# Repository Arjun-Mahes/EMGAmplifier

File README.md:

made an EMG amplifier PCB from scratch that streams filtered raw and enveloped outputs wirelessly using an ESP32

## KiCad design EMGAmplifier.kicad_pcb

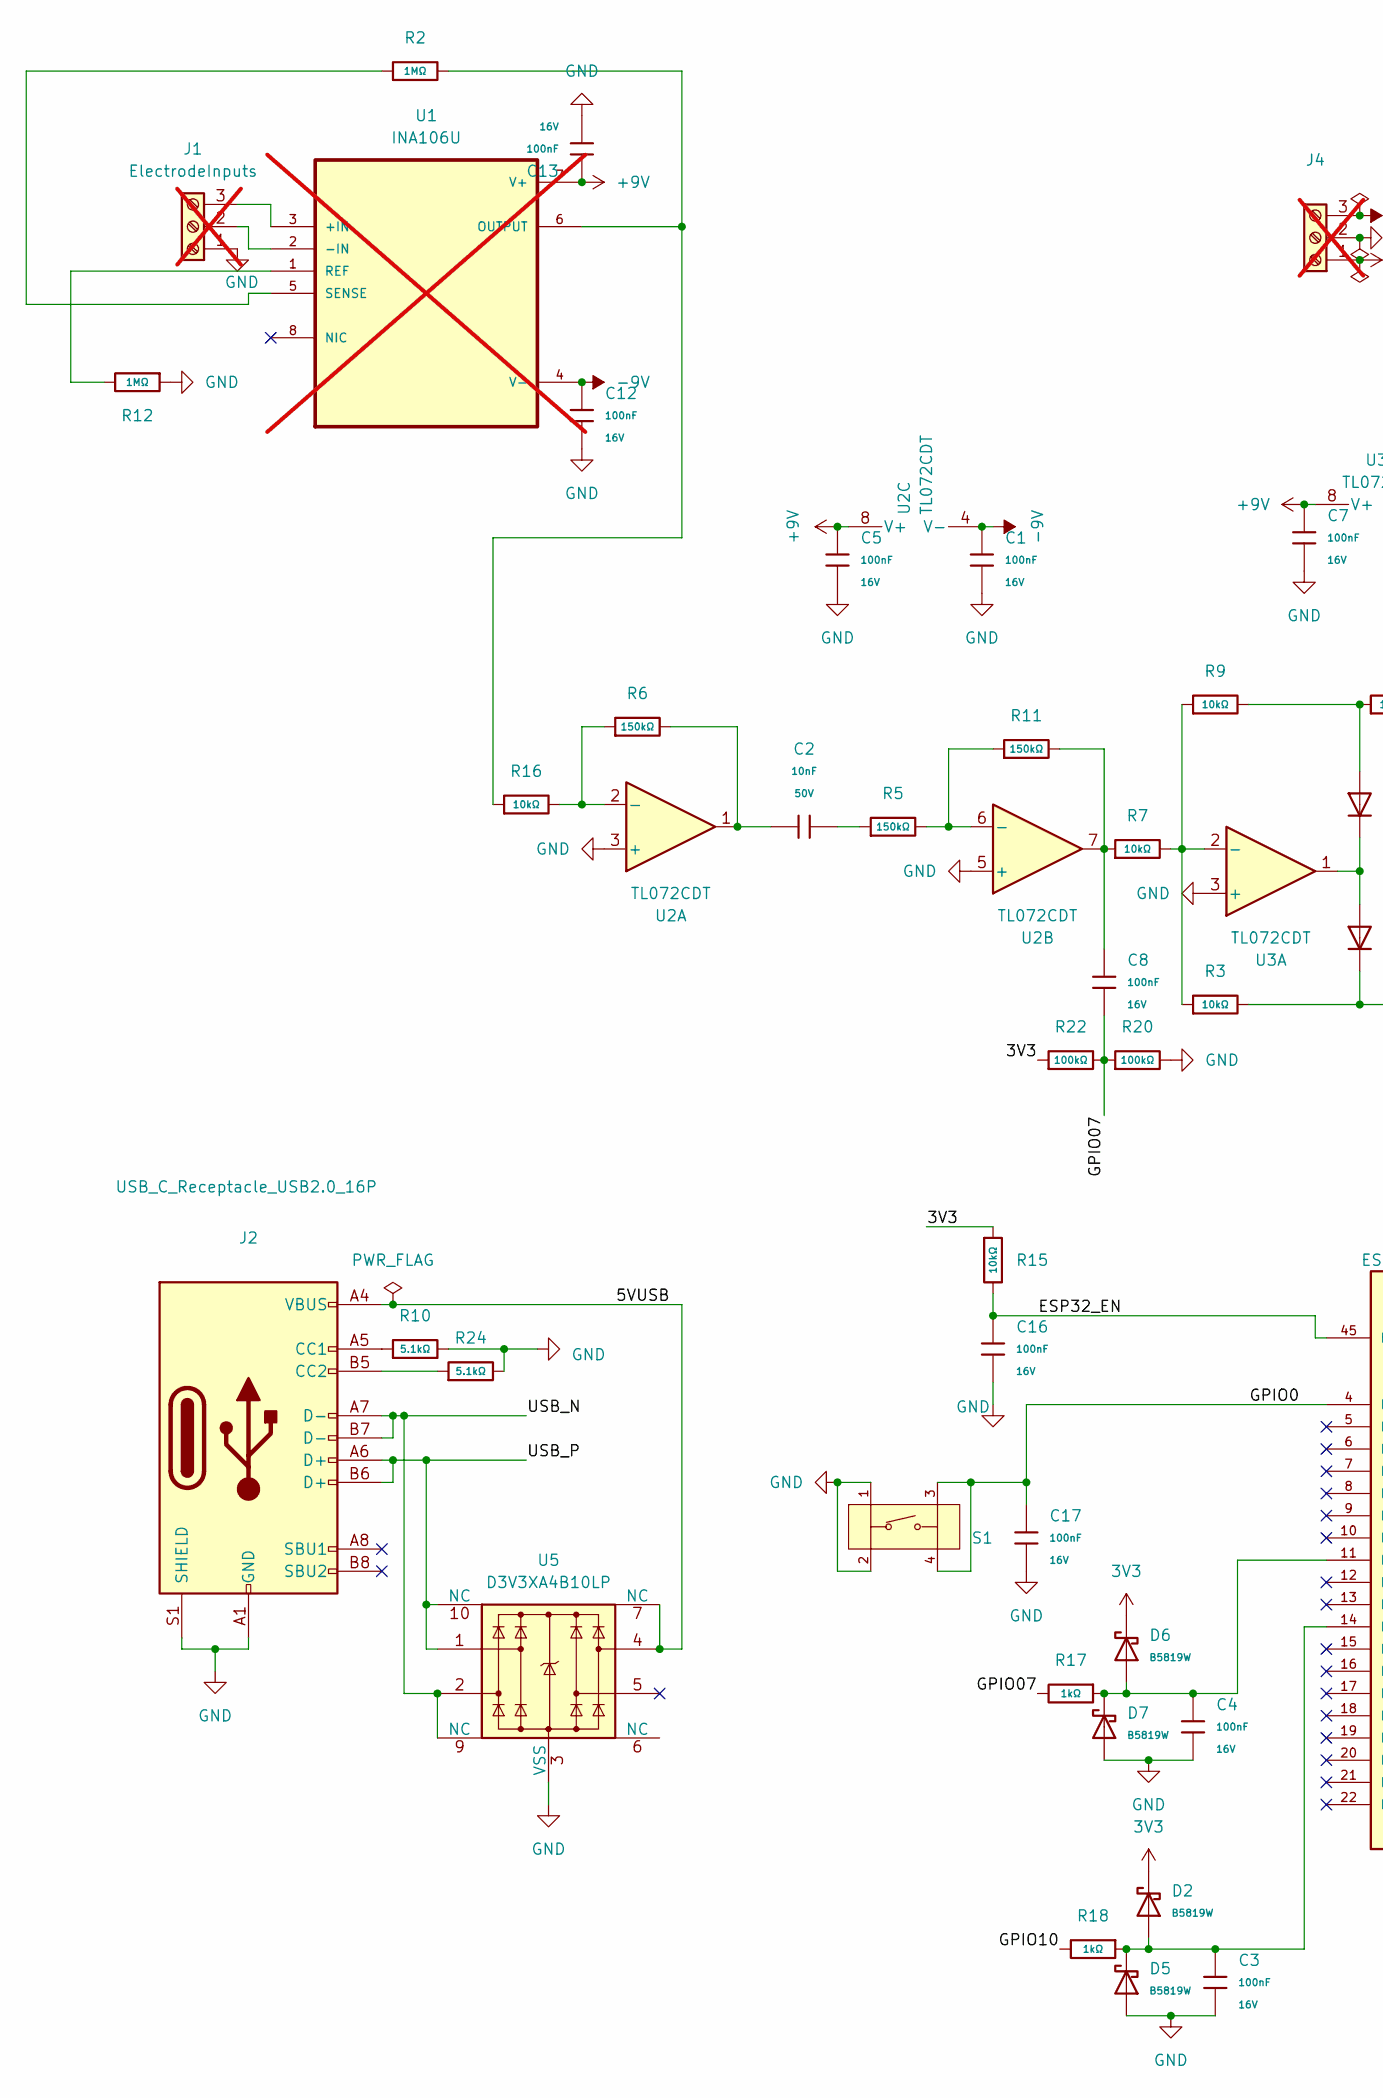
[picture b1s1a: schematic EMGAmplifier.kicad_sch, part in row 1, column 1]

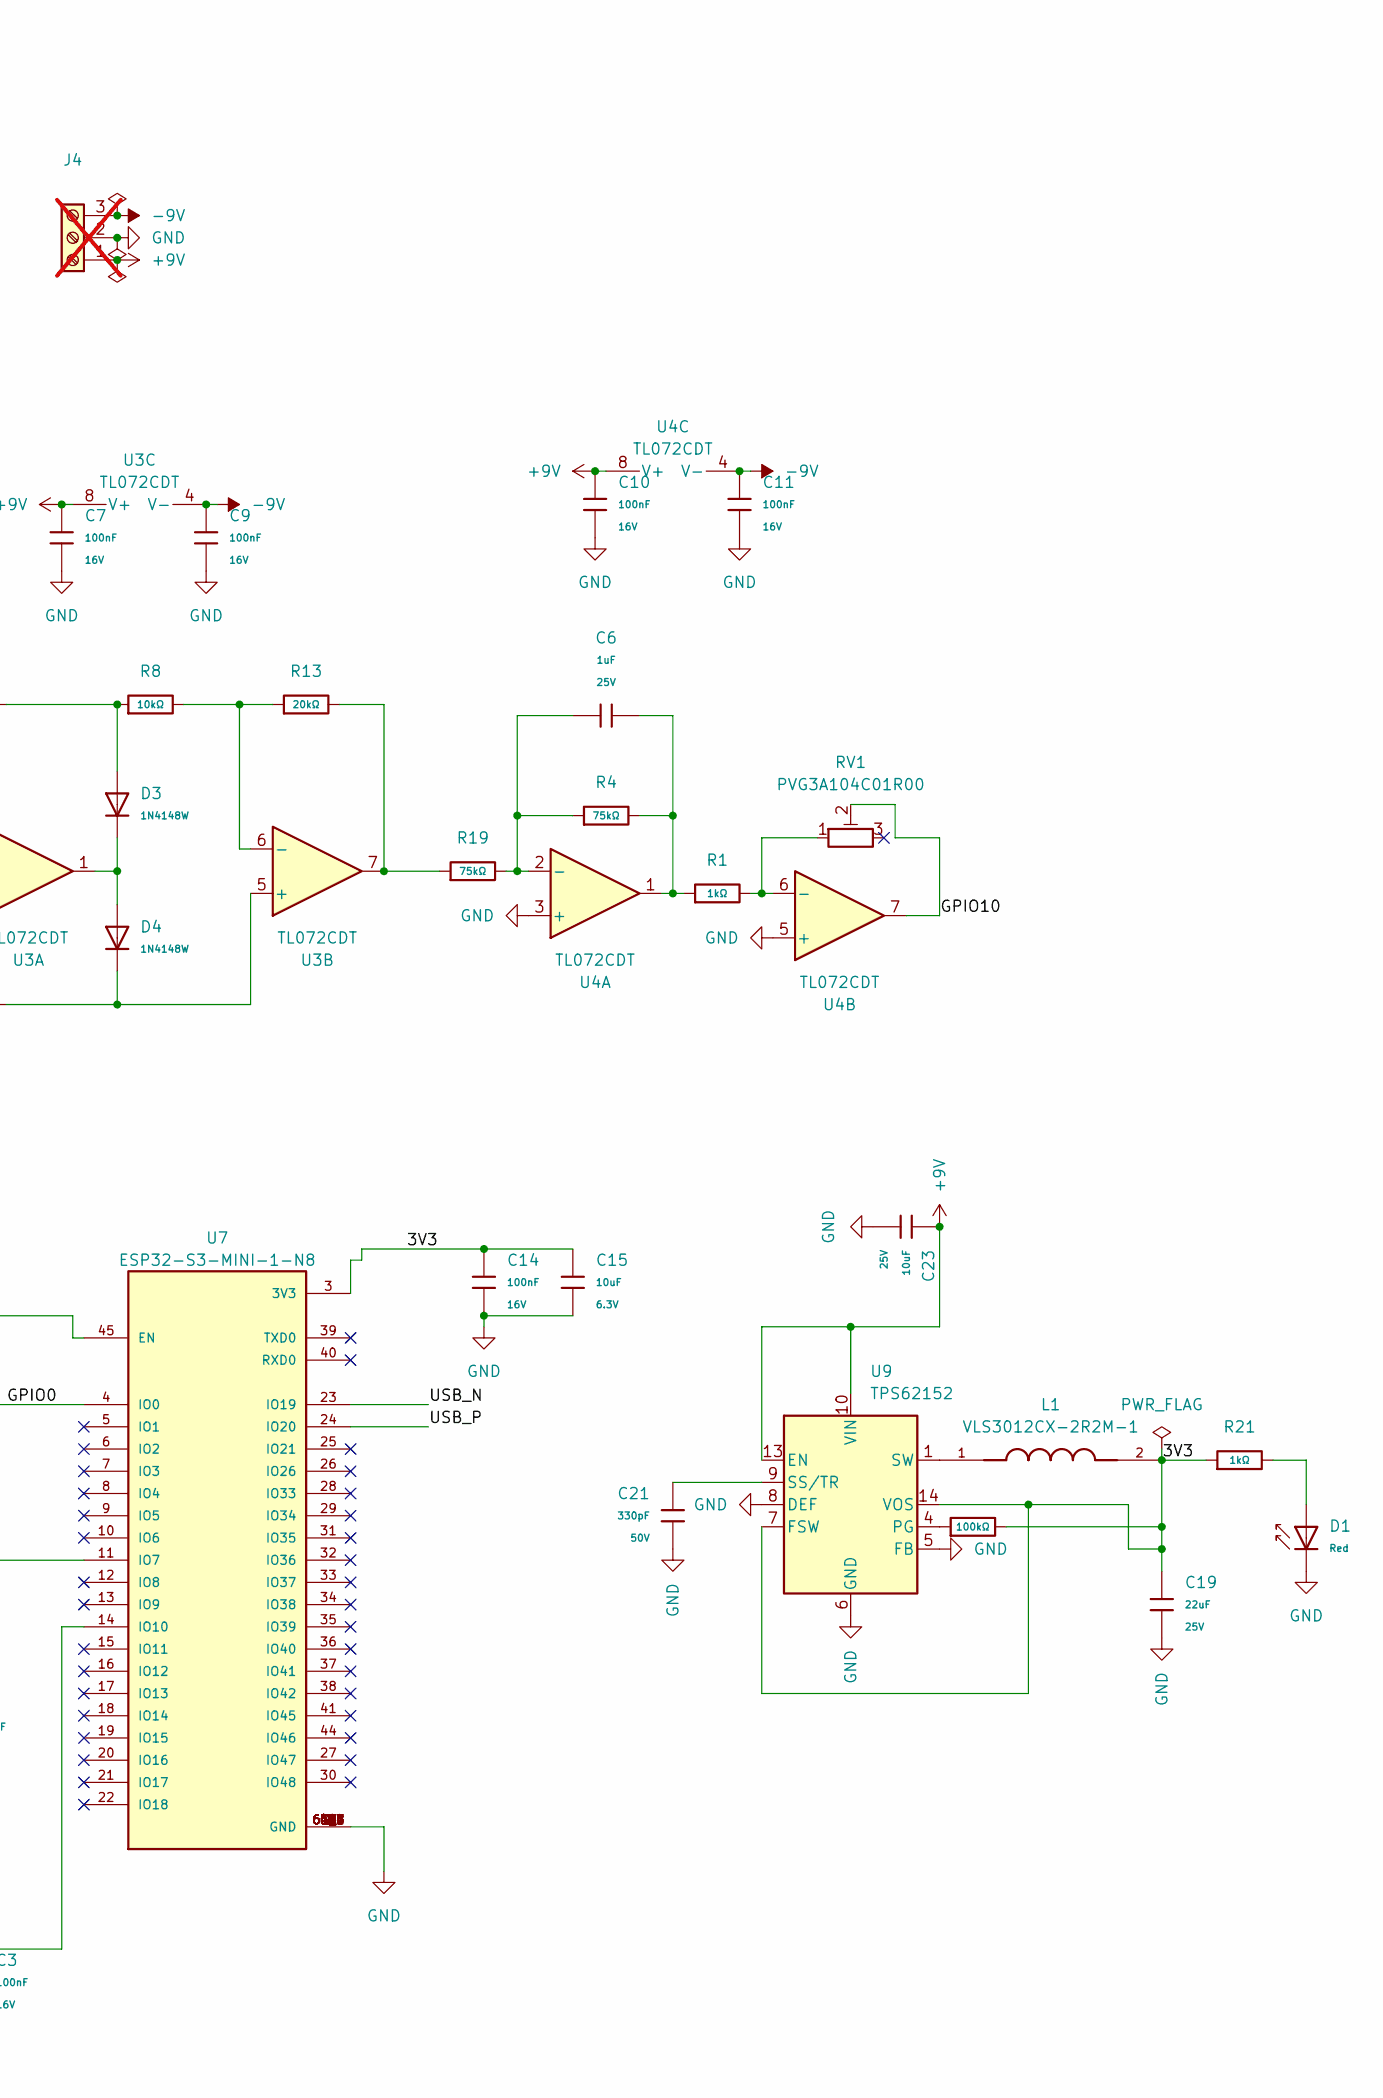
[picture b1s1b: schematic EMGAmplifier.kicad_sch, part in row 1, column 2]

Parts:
C1, C3, C4, C5, C7, C8, C9, C10, C11, C12, C13, C14, C16, C17: 100nF; C_0402; Voltage Rated 16V; Tolerance ±10%; Part CL05B104KO5NNNC; LCSC C1525
C2: 10nF; C_0402; Voltage Rated 50V; Tolerance ±10%; Part CL05B103KB5NNNC; LCSC C15195
C6: 1uF; C_0402; Voltage Rated 25V; Tolerance ±10%; Part CL05A105KA5NQNC; LCSC C52923
C15: 10uF; C_0402; Voltage Rated 6.3V; Tolerance ±20%; Part CL05A106MQ5NUNC; LCSC C15525
C19: 22uF; C_0805; Voltage Rated 25V; Tolerance ±20%; Part CL21A226MAQNNNE; LCSC C45783
C21: 330pF; C_0402; Voltage Rated 50V; Tolerance ±5%; Part CL05C331JB5NNNC; LCSC C13533
C23: 10uF; C_0603; Voltage Rated 25V; Tolerance ±20%; Part CL10A106MA8NRNC; LCSC C96446
D1: Red; D_0603; Part KT-0603R; LCSC C2286
D2, D5, D6, D7: B5819W; D_SOD-123; Forward Voltage (Vf@If) 900mV@3A; Reverse Voltage (Vr) 40V; Part B5819W; LCSC C64885
D3, D4: 1N4148W; D_SOD-123; Forward Voltage (Vf@If) 1V@50mA; Reverse Voltage (Vr) 75V; Part 1N4148W; LCSC C81598
J1: ElectrodeInputs; SAMESKY_TB0011-350-03BE; not fitted
J2: USB_C_Receptacle_USB2.0_16P; USB_C_Receptacle_GCT_USB4105-xx-A_16P_TopMnt_Horizontal; LCSC C3020560
J4: SAMESKY_TB0011-350-03BE; not fitted
L1: VLS3012CX-2R2M-1; IND_VLS3012CX-2R2M-1; PARTREV N/A; LCSC C2683174
R1, R17, R18, R21: 1kΩ; R_0402; Overload Voltage (Max) 50V; Tolerance ±1%; Part 0402WGF1001TCE; LCSC C11702
R2, R12: 1MΩ; R_0402; Overload Voltage (Max) 50V; Tolerance ±1%; Part 0402WGF1004TCE; LCSC C26083
R3, R7, R8, R9, R15, R16: 10kΩ; R_0402; Overload Voltage (Max) 50V; Tolerance ±1%; Part 0402WGF1002TCE; LCSC C25744
R4, R19: 75kΩ; R_0603; Overload Voltage (Max) 75V; Tolerance ±1%; Part 0603WAF7502T5E; LCSC C23242
R5, R6, R11: 150kΩ; R_0603; Overload Voltage (Max) 75V; Tolerance ±1%; Part 0603WAF1503T5E; LCSC C22807
R10, R24: 5.1kΩ; R_0402; Overload Voltage (Max) 50V; Tolerance ±1%; Part 0402WGF5101TCE; LCSC C25905
R13: 20kΩ; R_0402; Overload Voltage (Max) 50V; Tolerance ±1%; Part 0402WGF2002TCE; LCSC C25765
R14, R20, R22: 100kΩ; R_0402; Overload Voltage (Max) 50V; Tolerance ±1%; Part 0402WGF1003TCE; LCSC C25741
RV1: PVG3A104C01R00; RES_C01R00-L; LCSC C5713245
S1: Tactile Button, 160gf; SW-SMD_4P-L5.1-W5.1-P3.70-LS6.5-TL-2; Voltage Rating (Dc) 12V; Part TS-1187A-B-A-B; LCSC C318884
U1: INA106U; SOIC127P599X175-8N; not fitted
U2, U3, U4: TL072CDT; SOIC-8_L5.0-W4.0-P1.27-LS6.0-BL; Voltage - Input Offset(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 3mV; Part TL072CDT; LCSC C6961
U5: D3V3XA4B10LP; Diodes_UDFN-10_1x2.5mm_P0.5mm; LCSC C1980462
U7: ESP32-S3-MINI-1-N8; XCVR_ESP32-S3-MINI-1-N8; PARTREV v0.6; LCSC C2913206
U9: TPS62152; VQFN-16-1EP_3x3mm_P0.5mm_EP1.68x1.68mm_ThermalVias; LCSC C2070611

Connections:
3V3: C14.1, C15.1, C19.1, D2.1, D6.1, L1.2, R14.2, R15.1, R21.1, R22.1, U7.3 (3V3), U9.7 (FSW), U9.14 (VOS)
+9V: C5.1, C7.1, C10.1, C13.1, C23.1, J4.1, U1.7 (V+), U2.8 (V+), U3.8 (V+), U4.8 (V+), U9.10 (VIN), U9.11 (VIN), U9.12 (VIN), U9.13 (EN)
-9V: C1.1, C9.1, C11.1, C12.1, J4.3, U1.4 (V-), U2.4 (V-), U3.4 (V-), U4.4 (V-)
/5VUSB: J2.A4 (VBUS), J2.A9 (VBUS), J2.B4 (VBUS), J2.B9 (VBUS), U5.4, U5.7 (NC)
/ESP32_EN: C16.1, R15.2, U7.45 (EN)
/GPIO0: C17.1, S1.3 (C), S1.4 (D), U7.4 (IO0)
/GPIO07: C8.2, R17.2, R20.1, R22.2
/GPIO10: R18.2, RV1.2, U4.7
/USB_N: J2.A7 (D-), J2.B7 (D-), U5.2, U5.9 (NC), U7.23 (IO19)
/USB_P: J2.A6 (D+), J2.B6 (D+), U5.1, U5.10 (NC), U7.24 (IO20)
GND: C1.2, C3.2, C4.2, C5.2, C7.2, C9.2, C10.2, C11.2, C12.2, C13.2, C14.2, C15.2, C16.2, C17.2, C19.2, C21.2, C23.2, D1.1, D5.2, D7.2, J1.1, J2.A1 (GND), J2.A12 (GND), J2.B1 (GND), J2.B12 (GND), J2.S1 (SHIELD), J4.2, R10.2, R12.1, R20.2, R24.2, S1.1 (A), S1.2 (B), U2.3 (+), U2.5 (+), U3.3 (+), U4.3 (+), U4.5 (+), U5.3 (VSS), U5.8 (VSS), U7.1 (GND), U7.2 (GND), U7.42 (GND), U7.43 (GND), U7.46 (GND), U7.47 (GND), U7.48 (GND), U7.49 (GND), U7.50 (GND), U7.51 (GND), U7.52 (GND), U7.53 (GND), U7.54 (GND), U7.55 (GND), U7.56 (GND), U7.57 (GND), U7.58 (GND), U7.59 (GND), U7.60 (GND), U7.61 (GND), U7.61_1 (GND), U7.61_2 (GND), U7.61_3 (GND), U7.61_4 (GND), U7.61_5 (GND), U7.61_6 (GND), U7.61_7 (GND), U7.61_8 (GND), U7.62 (GND), U7.63 (GND), U7.64 (GND), U7.65 (GND), U9.5 (FB), U9.6 (GND), U9.8 (DEF), U9.15 (GND), U9.16 (GND), U9.17 (GND)
unnamed: C2.1, R6.2, U2.1
unnamed: C2.2, R5.1
unnamed: C6.2, R1.1, R4.2, U4.1
unnamed: C8.1, R7.1, R11.2, U2.7
unnamed: D1.2, R21.2
unnamed: D3.1, D4.2, U3.1
unnamed: D3.2, R8.1, R9.2
unnamed: J1.2, U1.2 (-IN)
unnamed: J1.3, U1.3 (+IN)
unnamed: J2.A5 (CC1), R10.1
unnamed: J2.B5 (CC2), R24.1
unnamed: L1.1, U9.1 (SW), U9.2 (SW), U9.3 (SW)
unnamed: R13.2, R19.1, U3.7
unnamed: R2.2, R16.1, U1.6 (OUTPUT)
unnamed: R12.2, U1.1 (REF)
unnamed: R2.1, U1.5 (SENSE)
unnamed: R6.1, R16.2, U2.2 (-)
unnamed: R5.2, R11.1, U2.6 (-)
unnamed: R3.1, R7.2, R9.1, U3.2 (-)
unnamed: D4.1, R3.2, U3.5 (+)
unnamed: R8.2, R13.1, U3.6 (-)
unnamed: C6.1, R4.1, R19.2, U4.2 (-)
unnamed: R1.2, RV1.1, U4.6 (-)
unnamed: C4.1, D6.2, D7.1, R17.1, U7.11 (IO7)
unnamed: C3.1, D2.2, D5.1, R18.1, U7.14 (IO10)
unnamed: R14.1, U9.4 (PG)
unnamed: C21.1, U9.9 (SS/TR)

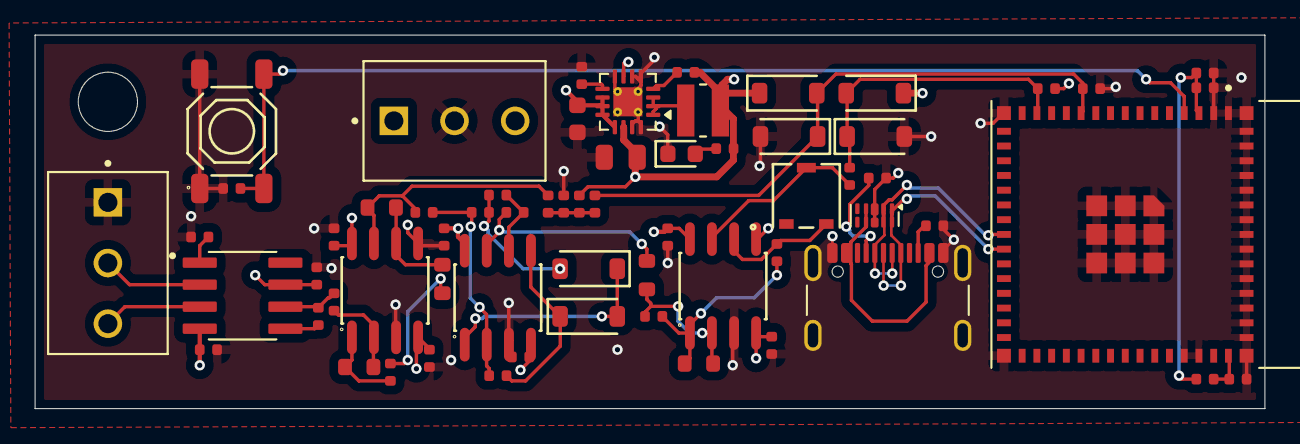
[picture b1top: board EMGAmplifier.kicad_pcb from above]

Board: 4 copper layers, 71.0 x 21.6 mm, 63 parts (0 on the bottom side), 38 nets.

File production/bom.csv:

Designator,Footprint,Quantity,Value,LCSC Part #
"C1, C10, C11, C12, C13, C14, C16, C17, C3, C5, C7, C9",C_0402,12,100nF,C1525
C15,C_0402,1,10uF,C15525
C19,C_0805,1,22uF,C45783
C2,C_0402,1,10nF,C15195
C21,C_0402,1,330pF,C13533
C23,C_0603,1,10uF,C96446
C6,C_0402,1,1uF,C52923
D1,D_0603,1,Red,C2286
"D2, D5",D_SOD-123,2,B5819W,C64885
"D3, D4",D_SOD-123,2,1N4148W,C81598
J2,USB_C_Receptacle_GCT_USB4105-xx-A_16P_TopMnt_Horizontal,1,USB_C_Receptacle_USB2.0_16P,C3020560
L1,IND_VLS3012CX-2R2M-1,1,VLS3012CX-2R2M-1,C2683174
"R1, R18, R21",R_0402,3,1kΩ,C11702
"R10, R24",R_0402,2,5.1kΩ,C25905
"R11, R5, R6",R_0603,3,150kΩ,C22807
"R12, R2",R_0402,2,1MΩ,C26083
R13,R_0402,1,20kΩ,C25765
R14,R_0402,1,100kΩ,C25741
"R15, R16, R3, R7, R8, R9",R_0402,6,10kΩ,C25744
"R19, R4",R_0603,2,75kΩ,C23242
RV1,RES_C01R00-L,1,PVG3A104C01R00,C5713245
"S1, S2",SW-SMD_4P-L5.1-W5.1-P3.70-LS6.5-TL-2,2,"Tactile Button, 160gf",C318884
"U2, U3, U4",SOIC-8_L5.0-W4.0-P1.27-LS6.0-BL,3,TL072CDT,C6961
U5,Diodes_UDFN-10_1x2.5mm_P0.5mm,1,D3V3XA4B10LP,C1980462
U7,XCVR_ESP32-S3-MINI-1-N8,1,ESP32-S3-MINI-1-N8,C2913206
U9,VQFN-16-1EP_3x3mm_P0.5mm_EP1.68x1.68mm_ThermalVias,1,TPS62152,C2070611
